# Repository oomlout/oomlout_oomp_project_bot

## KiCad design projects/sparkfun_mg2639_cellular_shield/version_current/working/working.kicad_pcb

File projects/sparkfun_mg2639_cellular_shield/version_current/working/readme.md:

# OOMP Project  
## MG2639_Cellular_Shield  by sparkfun  
  
oomp key: oomp_projects_flat_sparkfun_mg2639_cellular_shield  
(snippet of original readme)  
  
**Note:Retired Product**  
This product has been retired from our catalog and is no longer for sale. This page is made available for those looking for datasheets and the simply curious.  
  
SparkFun MG2639 Cellular Shield  
=========================  

[*SparkFun MG2639 Cellular Shield (CEL-13120)*](https://www.sparkfun.com/products/13120)  
  
The SparkFun MG2639 Cellular shield is an Arduino compatible shield that gives the user access to the MG2639_V3 GSM+GPS module. The module is capable of accquiring a GPS location as well as communication with GSM networks all over the world. Phonecalls can be made, texts sent, and data pushed to and read from web pages. All the supporting circuitry is provided including translation from 2.8V of the module to a user selectable 3.3V or 5V.  
  
The main interface is two software serial ports.  
  
Power can be provided either from the Arduino board's VIN or from an external battery such as a lithium polymer.  
  
Repository Contents  
-------------------  
  
* **/Firmware** - Example sketches that work without the Arduino library.  
* **/Hardware** - Schematic and PCB layout for the shield. Also includes an eagle library containing the various custom footprints for this shield. Specifically the MG2639 footprint.  
* **/Documentation** - The AT command set, hardware guide, and various other datasheets.  
* **/Libr  
  full source readme at [readme_src.md](readme_src.md)  
  
source repo at: [https://github.com/sparkfun/MG2639_Cellular_Shield](https://github.com/sparkfun/MG2639_Cellular_Shield)  
## Board  

## Schematic  

[schematic pdf](working_schematic.pdf)  
## Images

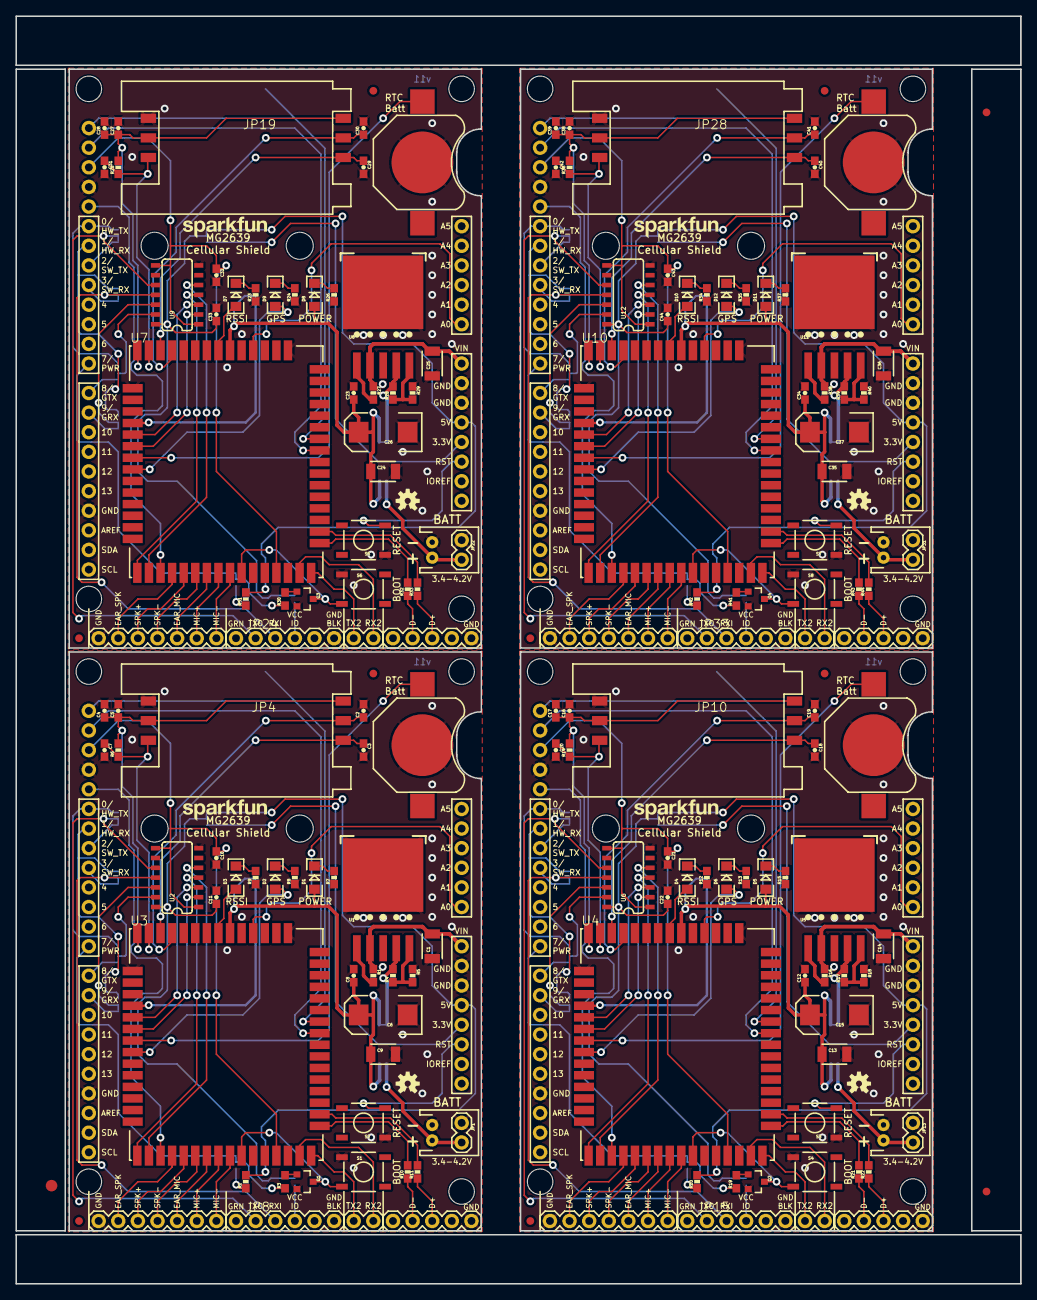
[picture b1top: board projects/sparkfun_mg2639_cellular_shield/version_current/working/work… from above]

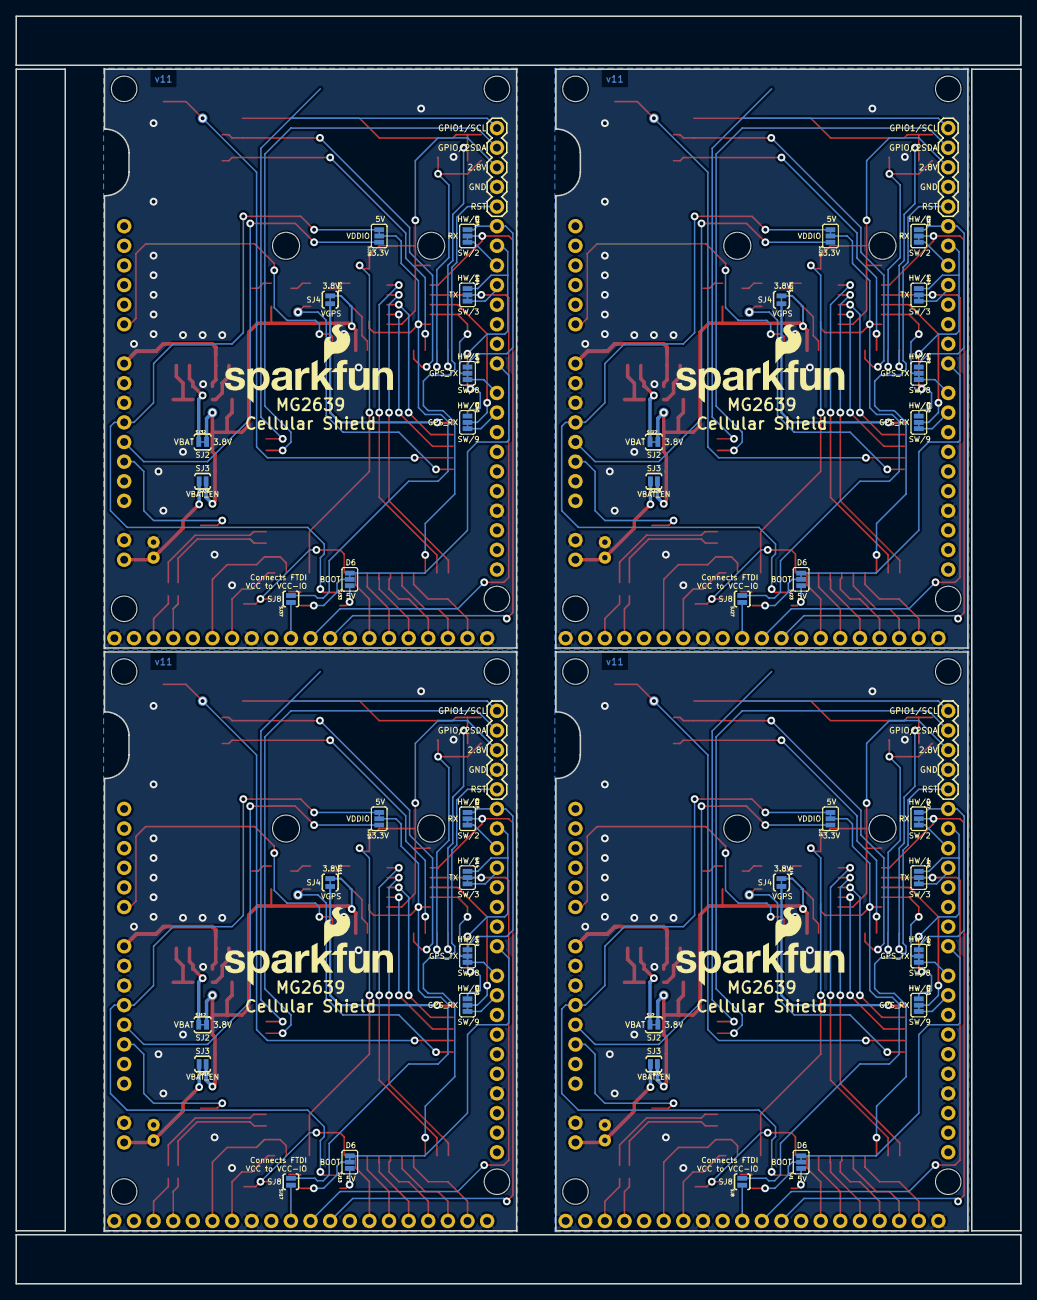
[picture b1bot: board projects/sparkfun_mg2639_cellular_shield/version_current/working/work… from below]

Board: 2 copper layers, 130.0 x 164.1 mm, 263 parts (60 on the bottom side), 236 nets.

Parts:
@HOLE0, @HOLE1, @HOLE2, @HOLE3, @HOLE4, @HOLE5, @HOLE6, @HOLE7: (no value)
BAT1, BAT2, BAT3, BAT4: 12mm coincell; BATTCON_12MM
C1, C9, C13, C14, C24, C25, C35, C36: 10uF; 1210
C2, C3, C7, C18, C19, C20, C29, C30, C31, C40, C41, C42: 33pF; 0603-CAP
C4, C17, C28, C39: 1.0uF; 0603-CAP
C5, C8, C10, C11, C12, C16, C21, C22, C23, C27, C32, C33, C34, C38, C43, C44: 0.1uF; 0603-CAP
C6, C15, C26, C37: 100uF; EIA7343
D1, D5, D8, D11: RED; LED-1206
D2, D6, D9, D12: YELLOW; LED-1206
D3, D4, D7, D10: GREEN; LED-1206
E$1: FIDUCIAL-1.5X3
E$4, E$5: FIDUCIAL-1X2
FID1, FID2, FID3, FID4, FID5, FID6, FID7, FID8: FIDUCIAL1X2; FIDUCIAL-1X2
JP1, JP13, JP22, JP31: LiPo; JST-2-PTH
JP2, JP16, JP25, JP34: M02PTH; 1X02
JP3, JP11, JP20, JP29: ARDUINO_R3_SHIELD; UNO_R3_SHIELD_NOLABELS
JP4, JP10, JP19, JP28: SIMHOLDER
JP5, JP12, JP21, JP30: AUDIO; 1X07
JP6, JP18, JP27, JP36: MISC; 1X05
JP7, JP17, JP26, JP35: UART2; 1X02
JP8, JP15, JP24, JP33: FTDI_BASICPTH; FTDI_BASIC
JP9, JP14, JP23, JP32: USB; 1X05
LOGO1, LOGO6, LOGO9, LOGO12: SFE_LOGO_NAME.1_INCH; SFE_LOGO_NAME_.1
LOGO2, LOGO5, LOGO8, LOGO11: SFE_LOGO_NAME_FLAME.2_INCH; SFE_LOGO_NAME_FLAME_.2
LOGO3, LOGO4, LOGO7, LOGO10: OSHW-LOGOS; OSHW-LOGO-S
Q1, Q2, Q3, Q4: MMBT2222A; SOT23-3
R1, R6, R14, R16, R25, R27, R36, R38: 10K; 0603-RES
R2, R5, R7, R8, R9, R12, R13, R15, R18, R20, R23, R24, R26, R29, R31, R34, R35, R37, R40, R42: 1K; 0603-RES
R3, R19, R30, R41: 4.7K; 0603
R4, R17, R28, R39: 2.2k; 0603-RES
R10, R11, R21, R22, R32, R33, R43, R44: 22; 0603-RES
S1, S4, S6, S8: BOOT; TACTILE-SWITCH-SMD
S2, S3, S5, S7: RESET; TACTILE-SWITCH-SMD
SJ1, SJ13, SJ23, SJ33: BOOT; PAD-JUMPER-3-2OF3_NC_BY_TRACE_YES_SILK_FULL_BOX
SJ2, SJ12, SJ22, SJ32: VBAT1; PAD-JUMPER-2-NC_BY_TRACE_YES_SILK
SJ3, SJ18, SJ28, SJ38: VBAT_EN; PAD-JUMPER-2-NO_YES_SILK
SJ4, SJ11, SJ21, SJ31: PAD-JUMPER-2-NC_BY_TRACE_YES_SILK
SJ5, SJ6, SJ7, SJ9, SJ10, SJ14, SJ15, SJ16, SJ19, SJ20, SJ24, SJ25, SJ26, SJ29, SJ30, SJ34, SJ35, SJ36, SJ39, SJ40: PAD-JUMPER-3-2OF3_NC_BY_TRACE_YES_SILK_FULL_BOX
SJ8, SJ17, SJ27, SJ37: FTDI_VCCIO; PAD-JUMPER-2-NO_YES_SILK
STANDOFF1, STANDOFF2, STANDOFF3, STANDOFF4, STANDOFF5, STANDOFF6, STANDOFF7, STANDOFF8, STANDOFF9, STANDOFF10, STANDOFF11, STANDOFF12, STANDOFF13, STANDOFF14, STANDOFF15, STANDOFF16: STAND-OFF
TP1, TP2, TP3, TP4, TP5, TP6, TP7, TP8, TP9, TP10, TP11, TP12: PAD.03X.05
U1, U5, U8, U11: SPX29302; Q5-DD_SPX29300
U2, U6, U9, U12: TXB0104; SO14
U3, U4, U7, U10: MG2639V3; MG2639

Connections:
3.3V: JP3.3.3V, SJ5.1
3.3V1: JP11.3.3V, SJ16.1
3.3V2: JP20.3.3V, SJ26.1
3.3V3: JP29.3.3V, SJ36.1
3.8V: C6.A, C8.1, C9.1, D1.A, SJ2.2, SJ3.1, SJ4.1, TP3.P$1, U3.6
3.8V1: C12.1, C13.1, C15.A, D5.A, SJ11.1, SJ12.2, SJ18.1, TP6.P$1, U4.6
3.8V2: C23.1, C24.1, C26.A, D8.A, SJ21.1, SJ22.2, SJ28.1, TP9.P$1, U7.6
3.8V3: C34.1, C35.1, C37.A, D11.A, SJ31.1, SJ32.2, SJ38.1, TP12.P$1, U10.6
5V: JP3.5V, R2.2, SJ5.3
5V1: JP11.5V, R20.2, SJ16.3
5V2: JP20.5V, R31.2, SJ26.3
5V3: JP29.5V, R42.2, SJ36.3
ADJUST: R4.1, R5.2, U1.5
ADJUST1: R17.1, R18.2, U5.5
ADJUST2: R28.1, R29.2, U8.5
ADJUST3: R39.1, R40.2, U11.5
EAR_L: JP5.6, U3.32
EAR_L1: JP12.6, U4.32
EAR_L2: JP21.6, U7.32
EAR_L3: JP30.6, U10.32
GND: BAT1.GND, C1.1, C2.2, C3.2, C4.2, C5.2, C6.C, C7.2, C8.2, C9.2, C10.2, C11.2, JP1.1, JP2.1, JP3.GND@0, JP3.GND@1, JP3.GND@2, JP4.C5, JP5.7, JP6.4, JP8.GND, JP9.1, Q1.2, R5.1, R7.1, R8.1, R9.1, S1.1, S2.1, U1.3, U1.6, U2.7, U3.1, U3.3, U3.5, U3.15, U3.17, U3.42
GND1: BAT2.GND, C12.2, C13.2, C14.1, C15.C, C16.2, C17.2, C18.2, C19.2, C20.2, C21.2, C22.2, JP10.C5, JP11.GND@0, JP11.GND@1, JP11.GND@2, JP12.7, JP13.1, JP14.1, JP15.GND, JP16.1, JP18.4, Q2.2, R12.1, R13.1, R15.1, R18.1, S3.1, S4.1, U4.1, U4.3, U4.5, U4.15, U4.17, U4.42, U5.3, U5.6, U6.7
GND2: BAT3.GND, C23.2, C24.2, C25.1, C26.C, C27.2, C28.2, C29.2, C30.2, C31.2, C32.2, C33.2, JP19.C5, JP20.GND@0, JP20.GND@1, JP20.GND@2, JP21.7, JP22.1, JP23.1, JP24.GND, JP25.1, JP27.4, Q3.2, R23.1, R24.1, R26.1, R29.1, S5.1, S6.1, U7.1, U7.3, U7.5, U7.15, U7.17, U7.42, U8.3, U8.6, U9.7
GND3: BAT4.GND, C34.2, C35.2, C36.1, C37.C, C38.2, C39.2, C40.2, C41.2, C42.2, C43.2, C44.2, JP28.C5, JP29.GND@0, JP29.GND@1, JP29.GND@2, JP30.7, JP31.1, JP32.1, JP33.GND, JP34.1, JP36.4, Q4.2, R34.1, R35.1, R37.1, R40.1, S7.1, S8.1, U10.1, U10.3, U10.5, U10.15, U10.17, U10.42, U11.3, U11.6, U12.7
GPIO1/SCL: JP6.1, U3.54
GPIO1/SCL1: JP18.1, U4.54
GPIO1/SCL2: JP27.1, U7.54
GPIO1/SCL3: JP36.1, U10.54
GPIO2/SDA: JP6.2, U3.53
GPIO2/SDA1: JP18.2, U4.53
GPIO2/SDA2: JP27.2, U7.53
GPIO2/SDA3: JP36.2, U10.53
GPS_FIX: D2.A, TP1.P$1, U3.22
GPS_FIX1: D6.A, TP4.P$1, U4.22
GPS_FIX2: D9.A, TP7.P$1, U7.22
GPS_FIX3: D12.A, TP10.P$1, U10.22
GPS_RTC: BAT1.PWR@1, TP2.P$1, U3.21
GPS_RTC1: BAT2.PWR@1, TP5.P$1, U4.21
GPS_RTC2: BAT3.PWR@1, TP8.P$1, U7.21
GPS_RTC3: BAT4.PWR@1, TP11.P$1, U10.21
GRX-2.8V: U2.3, U3.19
GRX-2.8V1: U4.19, U6.3
GRX-2.8V2: U7.19, U9.3
GRX-2.8V3: U10.19, U12.3
GRX-HV: SJ10.2, U2.12
GRX-HV1: SJ20.2, U6.12
GRX-HV2: SJ30.2, U9.12
GRX-HV3: SJ40.2, U12.12
GRX-SOFT: JP3.D9, SJ10.3
GRX-SOFT1: JP11.D9, SJ20.3
GRX-SOFT2: JP20.D9, SJ30.3
GRX-SOFT3: JP29.D9, SJ40.3
GTX-2.8V: U2.2, U3.20
GTX-2.8V1: U4.20, U6.2
GTX-2.8V2: U7.20, U9.2
GTX-2.8V3: U10.20, U12.2
GTX-HV: SJ9.2, U2.13
GTX-HV1: SJ19.2, U6.13
GTX-HV2: SJ29.2, U9.13
GTX-HV3: SJ39.2, U12.13
GTX-SOFT: JP3.D8, SJ9.3
GTX-SOFT1: JP11.D8, SJ19.3
GTX-SOFT2: JP20.D8, SJ29.3
GTX-SOFT3: JP29.D8, SJ39.3
MIC_N0: JP5.1, U3.37
MIC_N1: JP12.1, U4.37
MIC_N2: JP21.1, U7.37
MIC_N3: JP30.1, U10.37
MIC_P0: JP5.2, U3.36
MIC_P1: JP5.3, U3.35
MIC_P2: JP12.3, U4.35
MIC_P3: JP12.2, U4.36
MIC_P4: JP21.3, U7.35
MIC_P5: JP21.2, U7.36
MIC_P6: JP30.3, U10.35
MIC_P7: JP30.2, U10.36
unnamed: R1.2, U1.1
unnamed: JP9.4, R10.1
unnamed: Q1.1, R3.2
unnamed: R4.2, SJ2.1, U1.4
unnamed: R3.1, SJ1.2
unnamed: R2.1, SJ1.1
unnamed: D3.A, U3.7
unnamed: D3.C, R9.2
unnamed: D2.C, R8.2
unnamed: JP9.3, R11.1
unnamed: JP8.VCC, SJ8.1
unnamed: JP1.2, JP2.2, SJ3.2
unnamed: D5.C, R15.2
unnamed: R16.2, U5.1
unnamed: Q2.1, R19.2
unnamed: R19.1, SJ13.2
unnamed: D1.C, R7.2
unnamed: D4.A, U4.7
unnamed: D4.C, R12.2
unnamed: D6.C, R13.2
unnamed: R17.2, SJ12.1, U5.4
unnamed: R20.1, SJ13.1
unnamed: JP14.4, R21.1
unnamed: JP14.3, R22.1
unnamed: JP15.VCC, SJ17.1
unnamed: JP13.2, JP16.2, SJ18.2
unnamed: D8.C, R26.2
unnamed: R27.2, U8.1
unnamed: Q3.1, R30.2
unnamed: R30.1, SJ23.2
unnamed: D7.A, U7.7
unnamed: D7.C, R23.2
unnamed: D9.C, R24.2
unnamed: R28.2, SJ22.1, U8.4
unnamed: R31.1, SJ23.1
unnamed: JP23.4, R32.1
unnamed: JP23.3, R33.1
unnamed: JP24.VCC, SJ27.1
unnamed: JP22.2, JP25.2, SJ28.2
unnamed: D11.C, R37.2
unnamed: R38.2, U11.1
unnamed: Q4.1, R41.2
unnamed: R41.1, SJ33.2
unnamed: D10.A, U10.7
unnamed: D10.C, R34.2
unnamed: D12.C, R35.2
unnamed: R39.2, SJ32.1, U11.4
unnamed: R42.1, SJ33.1
unnamed: JP32.4, R43.1
unnamed: JP32.3, R44.1
unnamed: JP33.VCC, SJ37.1
unnamed: JP31.2, JP34.2, SJ38.2
ON/OFF: JP3.D7, SJ1.3
ON/OFF1: JP11.D7, SJ13.3
ON/OFF2: JP20.D7, SJ23.3
ON/OFF3: JP29.D7, SJ33.3
RECN: JP5.4, U3.34
RECN1: JP12.4, U4.34
RECN2: JP21.4, U7.34
RECN3: JP30.4, U10.34
RECP: JP5.5, U3.33
RECP1: JP12.5, U4.33
RECP2: JP21.5, U7.33
RECP3: JP30.5, U10.33
RESET: JP3.RES, S2.3
RESET1: JP11.RES, S3.3
RESET2: JP20.RES, S5.3
RESET3: JP29.RES, S7.3
RING: JP3.A0, U3.4
RING1: JP11.A0, U4.4
RING2: JP20.A0, U7.4
RING3: JP29.A0, U10.4
RX2-2.8V: JP7.1, U3.43
RX2-2.8V1: JP17.1, U4.43
RX2-2.8V2: JP26.1, U7.43
RX2-2.8V3: JP35.1, U10.43
RX-2.8V: U2.4, U3.29
RX-2.8V1: U4.29, U6.4
RX-2.8V2: U7.29, U9.4
RX-2.8V3: U10.29, U12.4
RX-HV: JP8.TXO, SJ6.2, U2.11
RX-HV1: JP15.TXO, SJ14.2, U6.11
RX-HV2: JP24.TXO, SJ24.2, U9.11
RX-HV3: JP33.TXO, SJ34.2, U12.11
RX-SOFT: JP3.D3, SJ6.3
RX-SOFT1: JP11.D3, SJ14.3
RX-SOFT2: JP20.D3, SJ24.3
RX-SOFT3: JP29.D3, SJ34.3
RXI: JP3.RX, SJ7.1, SJ9.1
RXI1: JP11.RX, SJ15.1, SJ19.1
RXI2: JP20.RX, SJ25.1, SJ29.1
RXI3: JP29.RX, SJ35.1, SJ39.1
SIM_CLK: C3.1, JP4.C3, U3.12
SIM_CLK1: C18.1, JP10.C3, U4.12
SIM_CLK2: C29.1, JP19.C3, U7.12
SIM_CLK3: C40.1, JP28.C3, U10.12
SIM_DATA: C7.1, JP4.C7, R6.1, U3.13
SIM_DATA1: C20.1, JP10.C7, R14.1, U4.13
SIM_DATA2: C31.1, JP19.C7, R25.1, U7.13
SIM_DATA3: C42.1, JP28.C7, R36.1, U10.13
SIM_RST: C2.1, JP4.C2, U3.11
SIM_RST1: C19.1, JP10.C2, U4.11
SIM_RST2: C30.1, JP19.C2, U7.11
SIM_RST3: C41.1, JP28.C2, U10.11
TX2-2.8V: JP7.2, U3.44
TX2-2.8V1: JP17.2, U4.44
TX2-2.8V2: JP26.2, U7.44
TX2-2.8V3: JP35.2, U10.44
TX-2.8V: U2.5, U3.30
TX-2.8V1: U4.30, U6.5
TX-2.8V2: U7.30, U9.5
TX-2.8V3: U10.30, U12.5
TX-HV: JP8.RXI, SJ7.2, U2.10
TX-HV1: JP15.RXI, SJ15.2, U6.10
TX-HV2: JP24.RXI, SJ25.2, U9.10
TX-HV3: JP33.RXI, SJ35.2, U12.10
TX-SOFT: JP3.D2, SJ7.3
TX-SOFT1: JP11.D2, SJ15.3
TX-SOFT2: JP20.D2, SJ25.3
TX-SOFT3: JP29.D2, SJ35.3
TXO: JP3.TX, SJ6.1, SJ10.1
TXO1: JP11.TX, SJ14.1, SJ20.1
TXO2: JP20.TX, SJ24.1, SJ30.1
TXO3: JP29.TX, SJ34.1, SJ40.1
USB+: R11.2, U3.46
USB+1: R22.2, U4.46
USB+2: R33.2, U7.46
USB+3: R44.2, U10.46
USB-: R10.2, U3.45
USB-1: R21.2, U4.45
USB-2: R32.2, U7.45
USB-3: R43.2, U10.45
VCCB: C11.1, SJ5.2, SJ8.2, U2.14
VCCB1: C22.1, SJ16.2, SJ17.2, U6.14
VCCB2: C33.1, SJ26.2, SJ27.2, U9.14
VCCB3: C44.1, SJ36.2, SJ37.2, U12.14
VDDIO: C10.1, JP6.3, U2.1, U2.8, U3.41
VDDIO1: C21.1, JP18.3, U4.41, U6.1, U6.8
VDDIO2: C32.1, JP27.3, U7.41, U9.1, U9.8
VDDIO3: C43.1, JP36.3, U10.41, U12.1, U12.8
VRAW: C1.2, JP3.VIN, R1.1, U1.2
VRAW1: C14.2, JP11.VIN, R16.1, U5.2
VRAW2: C25.2, JP20.VIN, R27.1, U8.2
VRAW3: C36.2, JP29.VIN, R38.1, U11.2
VSIM: C4.1, C5.1, JP4.C1, JP4.C6, R6.2, U3.14
VSIM1: C16.1, C17.1, JP10.C1, JP10.C6, R14.2, U4.14
VSIM2: C27.1, C28.1, JP19.C1, JP19.C6, R25.2, U7.14
VSIM3: C38.1, C39.1, JP28.C1, JP28.C6, R36.2, U10.14
V_GPS: SJ4.2, U3.18
V_GPS1: SJ11.2, U4.18
V_GPS2: SJ21.2, U7.18
V_GPS3: SJ31.2, U10.18
~PWRKEY1: Q2.3, S4.3, U4.38
~PWRKEY2: Q3.3, S6.3, U7.38
~PWRKEY3: Q4.3, S8.3, U10.38
~PWRKEY: Q1.3, S1.3, U3.38
~SYSRST1: JP18.5, U4.31
~SYSRST2: JP27.5, U7.31
~SYSRST3: JP36.5, U10.31
~SYSRST: JP6.5, U3.31

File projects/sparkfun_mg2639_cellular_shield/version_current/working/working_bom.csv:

Row,Description,Part,References,Value,Footprint,Quantity Per PCB,Status,Datasheet
1,,BATTERY12MM,BAT1,12mm coincell,BATTCON_12MM,1, ,
2,,33PF-50V-5%-(0603),C2 C3 C7,33pF,0603-CAP,3, ,
3,,0.1UF-25V(+80/-20%)(0603),C5 C8 C10 C11,0.1uF,0603-CAP,4, ,
4,,1.0UF-16V-10%(0603),C4,1.0uF,0603-CAP,1, ,
5,,10UF50V20%(1210),C1 C9,10uF,1210,2, ,
6,,100UF-10V-10%(TANT),C6,100uF,EIA7343,1, ,
7,,LED-GREENLARGE,D3,GREEN,LED-1206,1, ,
8,,LED-RED1206,D1,RED,LED-1206,1, ,
9,,LED-YELLOWLARGE,D2,YELLOW,LED-1206,1, ,
10,,FRAME-LEDGER,FRAME1,FRAME-LEDGER,CREATIVE_COMMONS,1, ,
11,,ARDUINO_R3_SHIELDNOLABELS,JP3,ARDUINO_R3_SHIELDNOLABELS,UNO_R3_SHIELD_NOLABELS,1, ,
12,,M07,JP5,AUDIO,1X07,1, ,
13,,FTDI_BASICPTH,JP8,FTDI_BASICPTH,FTDI_BASIC,1, ,
14,,M02JST-PTH-2,JP1,M02JST-PTH-2,JST-2-PTH,1, ,
15,,M02PTH,JP2 JP7,M02PTH,1X02,2, ,
16,,M05PTH,JP6,MISC,1X05,1, ,
17,,SIMHOLDERSIM,JP4,SIMHOLDER,SIMHOLDER,1, ,
18,,M05PTH,JP9,USB,1X05,1, ,
19,,OSHW-LOGOS,LOGO3,OSHW-LOGOS,OSHW-LOGO-S,1, ,
20,,SFE_LOGO_NAME.1_INCH,LOGO1,SFE_LOGO_NAME.1_INCH,SFE_LOGO_NAME_.1,1, ,
21,,SFE_LOGO_NAME_FLAME.2_INCH,LOGO2,SFE_LOGO_NAME_FLAME.2_INCH,SFE_LOGO_NAME_FLAME_.2,1, ,
22,,TRANSISTOR_NPNMMBT2222A,Q1,MMBT2222A,SOT23-3,1, ,
23,,22OHM1/10W1%(0603),R10 R11,22,0603-RES,2, ,
24,,1KOHM1/10W1%(0603),R2 R5 R7 R8 R9,1K,0603-RES,5, ,
25,,2.2KOHM1/10W1%(0603),R4,2.2k,0603-RES,1, ,
26,,4.7KOHM1/10W1%(0603),R3,4.7K,0603,1, ,
27,,10KOHM1/10W1%(0603)0603,R1 R6,10K,0603-RES,2, ,
28,,SWITCH-MOMENTARY-2SMD,S1 S2,SWITCH-MOMENTARY-2SMD,TACTILE-SWITCH-SMD,2, ,
29,,JUMPER-PAD-2-NC_BY_TRACE,SJ2 SJ4,JUMPER-PAD-2-NC_BY_TRACE,PAD-JUMPER-2-NC_BY_TRACE_YES_SILK,2, ,
30,,JUMPER-PAD-2-NOYES_SILK,SJ3 SJ8,JUMPER-PAD-2-NOYES_SILK,PAD-JUMPER-2-NO_YES_SILK,2, ,
31,,JUMPER-PAD-3-2OF3_NC_BY_TRACE,SJ1 SJ5 SJ6 SJ7 SJ9 SJ10,JUMPER-PAD-3-2OF3_NC_BY_TRACE,PAD-JUMPER-3-2OF3_NC_BY_TRACE_YES_SILK_FULL_BOX,6, ,
32,,STAND-OFF,STANDOFF1 STANDOFF2 STANDOFF3 STANDOFF4,STAND-OFF,STAND-OFF,4, ,
33,,MG2639V3,U3,MG2639V3,MG2639,1, ,
34,,SPX29302,U1,SPX29302,Q5-DD_SPX29300,1, ,
35,,TXB0104PWRSOIC14,U2,TXB0104,SO14,1, ,





Project info:
Schematic:,working
Variant:,default
Revision:,
Date:,2023-08-06_12-56-06
KiCad Version:,7.0.6-7.0.6~ubuntu22.04.1
Statistics:
Component Groups:,35
Component Count:,59 (0 SMD/ 0 THT)
Fitted Components:,59 (0 SMD/ 0 THT)
Number of PCBs:,1
Total Components:,59

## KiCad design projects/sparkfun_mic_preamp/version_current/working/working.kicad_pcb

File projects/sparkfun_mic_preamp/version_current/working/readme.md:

# OOMP Project  
## Mic_Preamp  by sparkfun  
  
oomp key: oomp_projects_flat_sparkfun_mic_preamp  
(snippet of original readme)  
  
Mic_Preamp  
==========  
[  
*SparkFun Mic Preamp (PRT-08872)*](https://www.sparkfun.com/products/8872)  
  
This breakout is a simple microphone preamp circuit for a wide range of microphone types.   
It enables you to attach mics to your larger stereo amplifier.  
  
Repository Contents  
-------------------  
* **/Hardware** - All Eagle design files (.brd, .sch)  

License Information  
-------------------  
The hardware is released under [Creative Commons ShareAlike 4.0 International](https://creativecommons.org/licenses/by-sa/4.0/).  
  
Distributed as-is; no warranty is given.  
  full source readme at [readme_src.md](readme_src.md)  
  
source repo at: [https://github.com/sparkfun/Mic_Preamp](https://github.com/sparkfun/Mic_Preamp)  
## Board  

## Schematic  

[schematic pdf](working_schematic.pdf)  
## Images

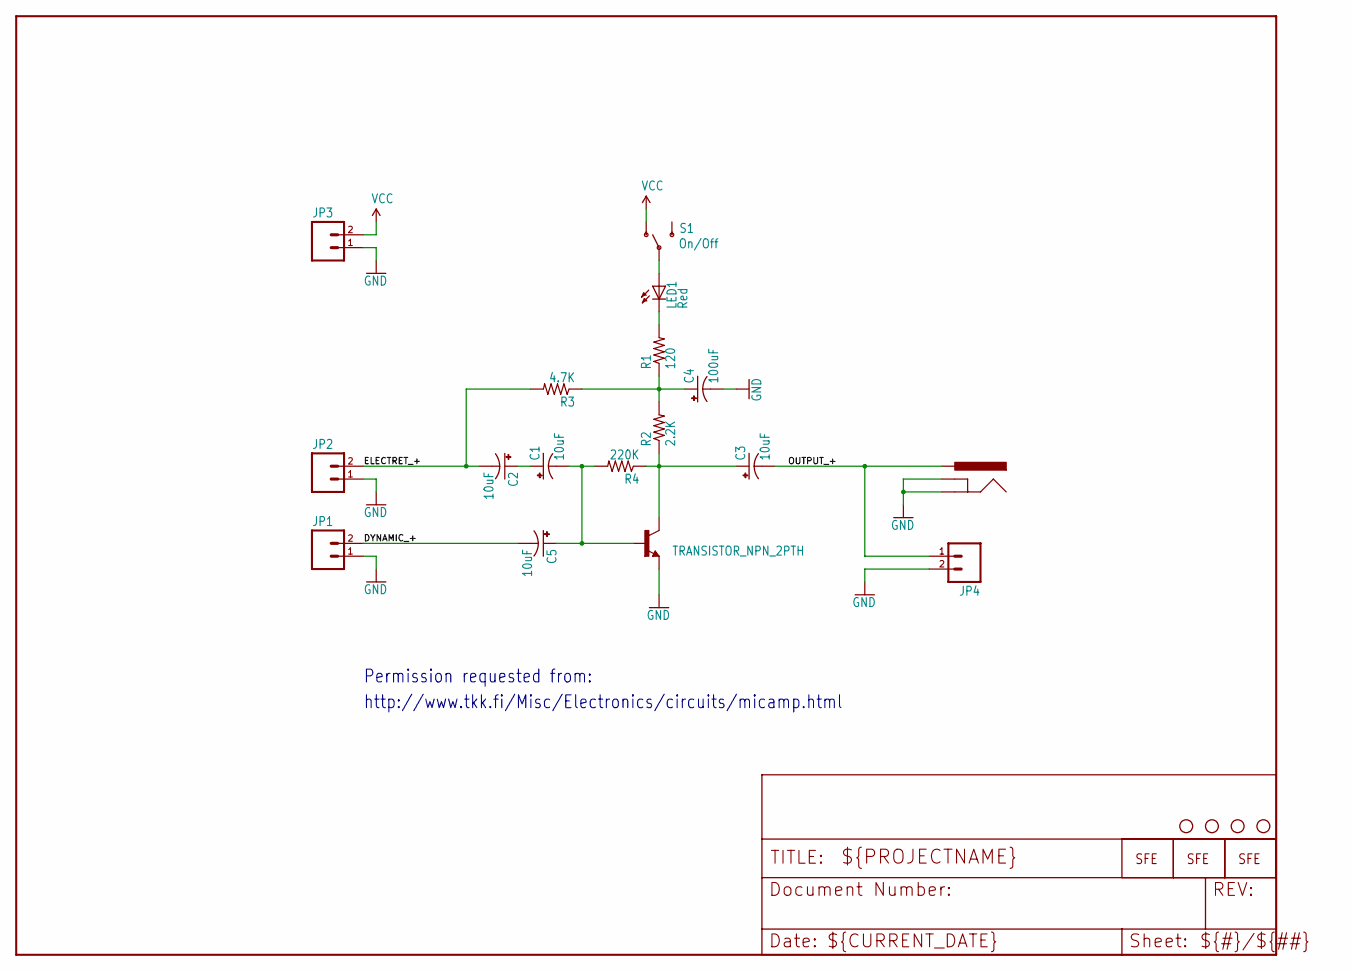
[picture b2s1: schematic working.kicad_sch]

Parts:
C1, C2, C3, C5: 10uF; CPOL-RADIAL-10UF-25V
C4: 100uF; CPOL-RADIAL-100UF-25V
J1: POWER_JACKRCA_LOCK; RCA_LOCK
JP1, JP2, JP3, JP4: M02PTH; 1X02
JP6: LOGO-SFENW2; SFE-NEW-WEB
LED1: Red; LED5MM
Q1: TRANSISTOR_NPN_2PTH; TO-92
R1: 120; AXIAL-0.3
R2: 2.2K; AXIAL-0.3
R3: 4.7K; AXIAL-0.3
R4: 220K; AXIAL-0.3
S1: On/Off; SWITCH-SPDT_LOCK.007S
U$1, U$6: LOGO-SFESK; SFE-LOGO-FLAME
U$2, U$3, U$4, U$5: STAND-OFF

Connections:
DYNAMIC_+: C5.2 (-), JP1.2
ELECTRET_+: C2.2 (-), JP2.2, R3.P$2 (2)
GND: C4.2 (-), J1.BARREL (GND), J1.SPRING (GNDBREAK), JP1.1, JP2.1, JP3.1, JP4.2, Q1.3 (E)
unnamed: LED1.K (C), R1.P$2 (2)
unnamed: C3.1 (+), Q1.1 (C), R2.P$1 (1), R4.P$1 (1)
unnamed: C4.1 (+), R1.P$1 (1), R2.P$2 (2), R3.P$1 (1)
unnamed: C1.2 (-), C5.1 (+), Q1.2 (B), R4.P$2 (2)
unnamed: C1.1 (+), C2.1 (+)
unnamed: LED1.A, S1.2
OUTPUT_+: C3.2 (-), J1.BREAK (PWR), JP4.1
VCC: JP3.2, S1.1 (O)

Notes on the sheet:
Permission requested from:
http://www.tkk.fi/Misc/Electronics/circuits/micamp.html

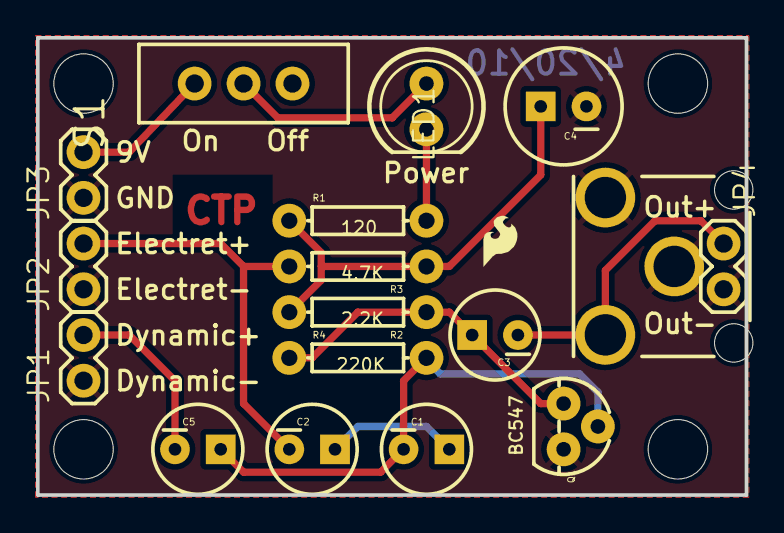
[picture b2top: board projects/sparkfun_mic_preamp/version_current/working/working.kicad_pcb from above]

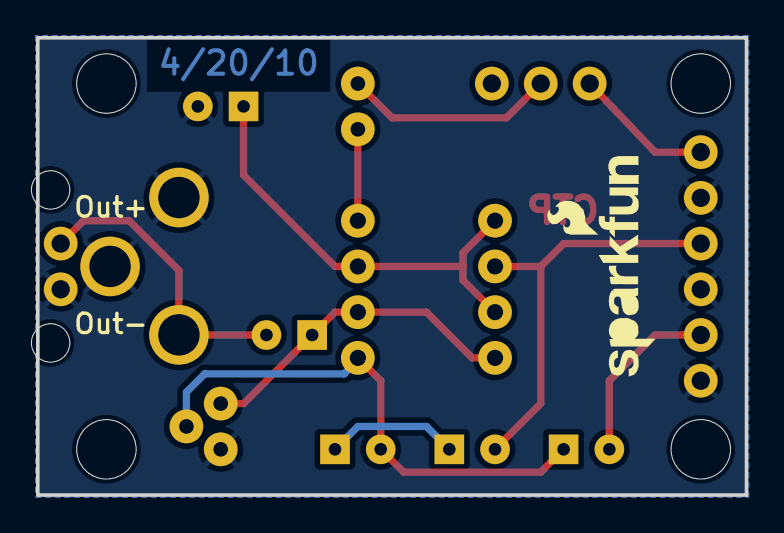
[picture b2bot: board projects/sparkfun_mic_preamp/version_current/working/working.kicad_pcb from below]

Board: 2 copper layers, 39.4 x 25.4 mm, 24 parts (2 on the bottom side), 11 nets.

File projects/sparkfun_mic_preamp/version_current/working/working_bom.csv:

"Id";"Designator";"Footprint";"Quantity";"Designation";"Supplier and ref";
1;"U$3,U$5,U$4,U$2";"STAND-OFF";4;"STAND-OFF";;;
2;"C2,C3,C1,C5";"CPOL-RADIAL-10UF-25V";4;"10uF";;;
3;"R3";"AXIAL-0.3";1;"4.7K";;;
4;"S1";"SWITCH-SPDT_LOCK.007S";1;"On/Off";;;
5;"LED1";"LED5MM";1;"Red";;;
6;"JP4,JP2,JP3,JP1";"1X02";4;"";;;
7;"C4";"CPOL-RADIAL-100UF-25V";1;"100uF";;;
8;"J1";"RCA_LOCK";1;"POWER_JACKRCA_LOCK";;;
9;"R1";"AXIAL-0.3";1;"120";;;
10;"R2";"AXIAL-0.3";1;"2.2K";;;
11;"Q1";"TO-92";1;"TRANSISTOR_NPN_2PTH";;;
12;"R4";"AXIAL-0.3";1;"220K";;;
13;"U$1,U$6";"SFE-LOGO-FLAME";2;"LOGO-SFESK";;;
14;"JP6";"SFE-NEW-WEB";1;"LOGO-SFENW2";;;

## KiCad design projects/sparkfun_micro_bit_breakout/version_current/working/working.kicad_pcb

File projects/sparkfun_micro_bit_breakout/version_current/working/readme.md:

# Micro_Bit_Breakout by sparkfun  
This is a harvested standardized copy of a project from github.  
The original project can be found at:  
https://github.com/sparkfun/Micro_Bit_Breakout  
Please consult that link for additional, details, files, and license information.  
Note: It was auto harvested and if the original repo had more than one board file or anything out of the ordinary the files here are likely not representative.

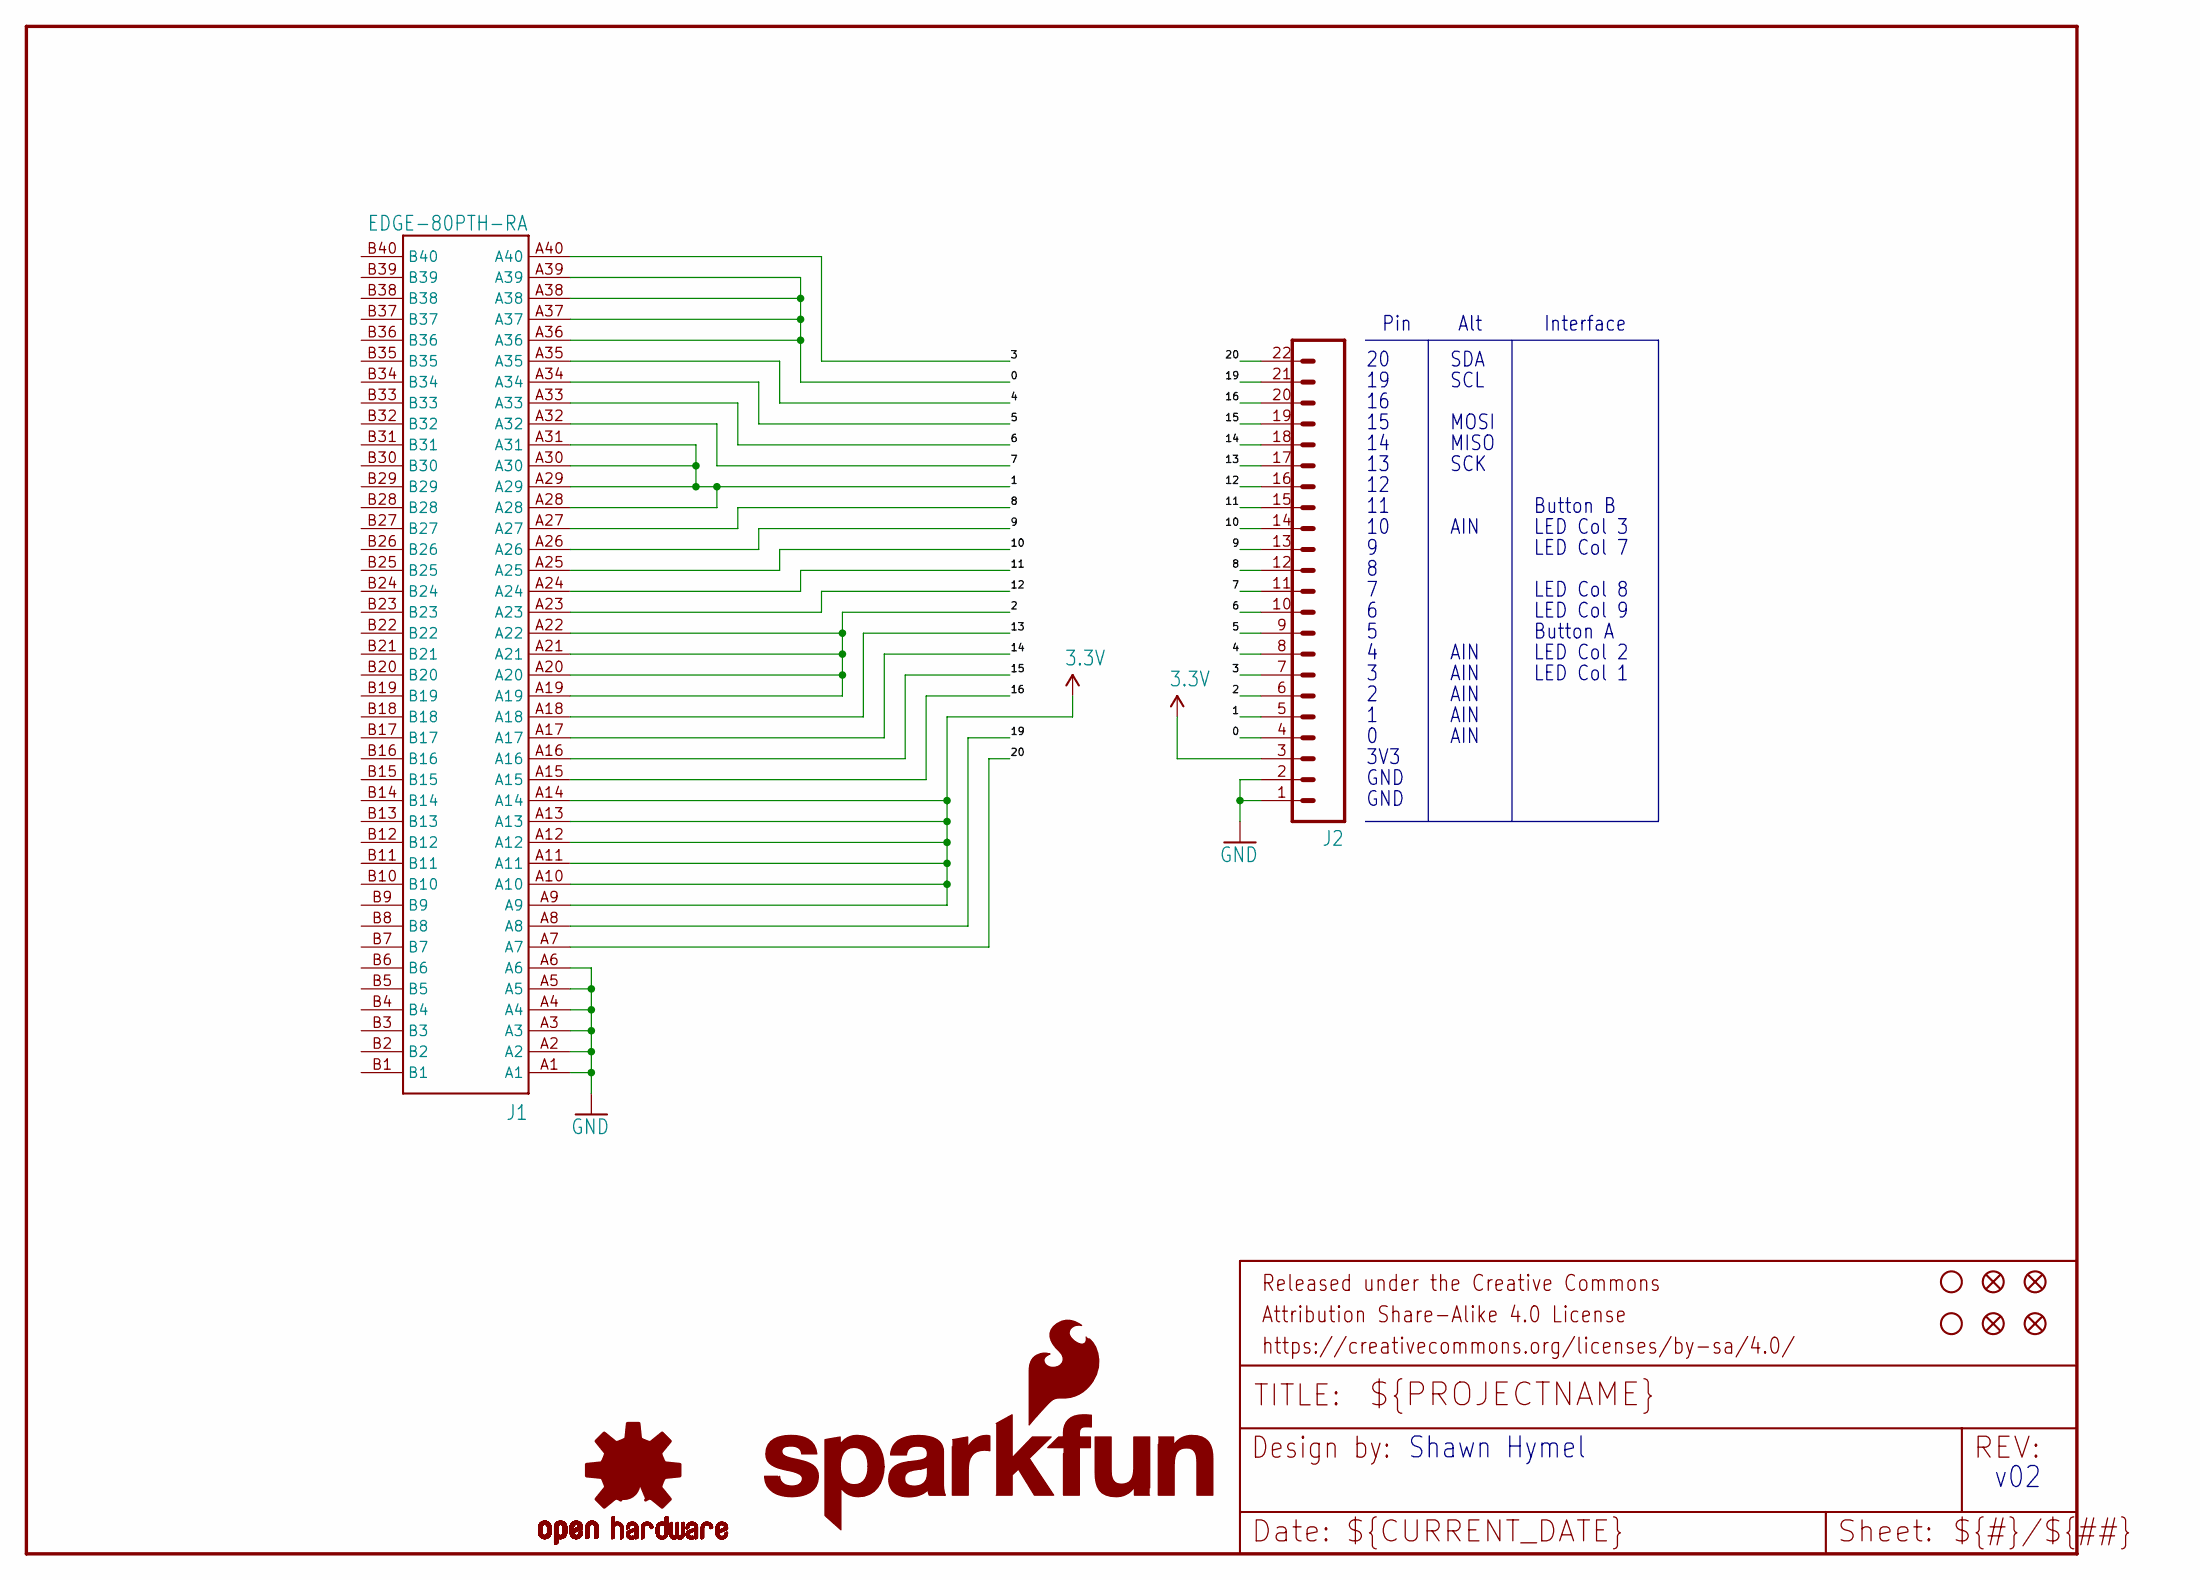
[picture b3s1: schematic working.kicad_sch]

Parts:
FD1, FD2, FD3, FD4: FIDUCIAL1X2; FIDUCIAL-1X2
FRAME1: FRAME-LETTER; CREATIVE_COMMONS
H1, H2: STAND-OFF
J1: EDGE-80PTH-RA; VEC-127-080-R
J2: M22PTH; 1X22
LOGO2: SFE_LOGO_NAME_FLAME.1_INCH; SFE_LOGO_NAME_FLAME_.1
LOGO3: OSHW-LOGOS; OSHW-LOGO-S

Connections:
0: J1.A36, J1.A37, J1.A38, J1.A39, J2.4
1: J1.A28, J1.A29, J1.A30, J1.A31, J2.5
2: J1.A19, J1.A20, J1.A21, J1.A22, J2.6
3: J1.A40, J2.7
3.3V: J1.A9, J1.A10, J1.A11, J1.A12, J1.A13, J1.A14, J2.3
4: J1.A35, J2.8
5: J1.A34, J2.9
6: J1.A33, J2.10
7: J1.A32, J2.11
8: J1.A27, J2.12
9: J1.A26, J2.13
10: J1.A25, J2.14
11: J1.A24, J2.15
12: J1.A23, J2.16
13: J1.A18, J2.17
14: J1.A17, J2.18
15: J1.A16, J2.19
16: J1.A15, J2.20
19: J1.A8, J2.21
20: J1.A7, J2.22
GND: J1.A1, J1.A2, J1.A3, J1.A4, J1.A5, J1.A6, J2.1, J2.2

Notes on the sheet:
LED Col 1
GND
LED Col 3
Pin
LED Col 2
3V3
AIN
SCL
MISO
Shawn Hymel
Button B
MOSI
LED Col 7
Alt
SDA
Button A
LED Col 9
LED Col 8
SCK
Interface
v02

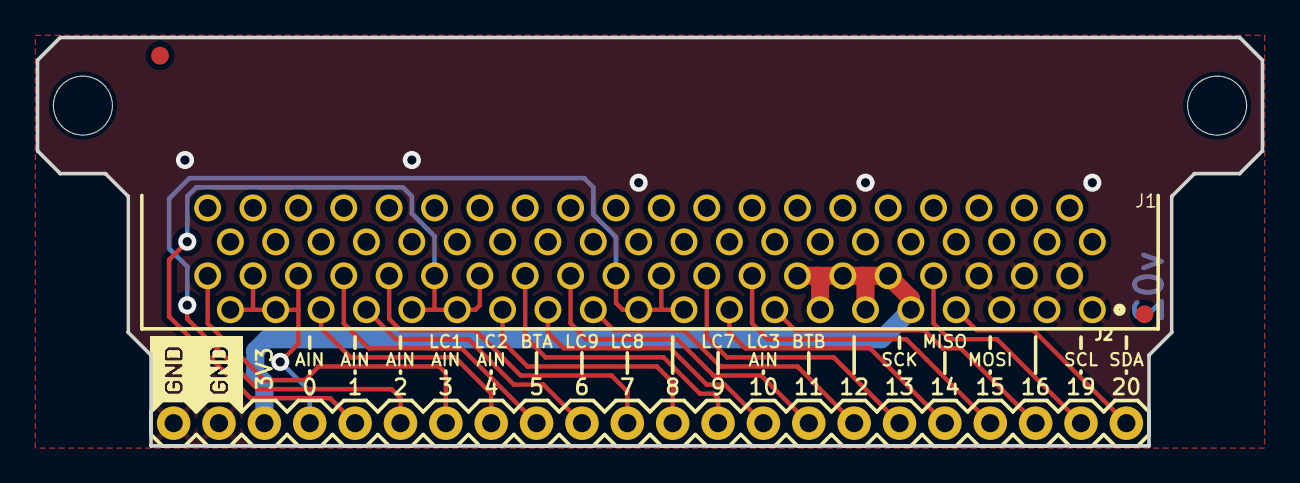
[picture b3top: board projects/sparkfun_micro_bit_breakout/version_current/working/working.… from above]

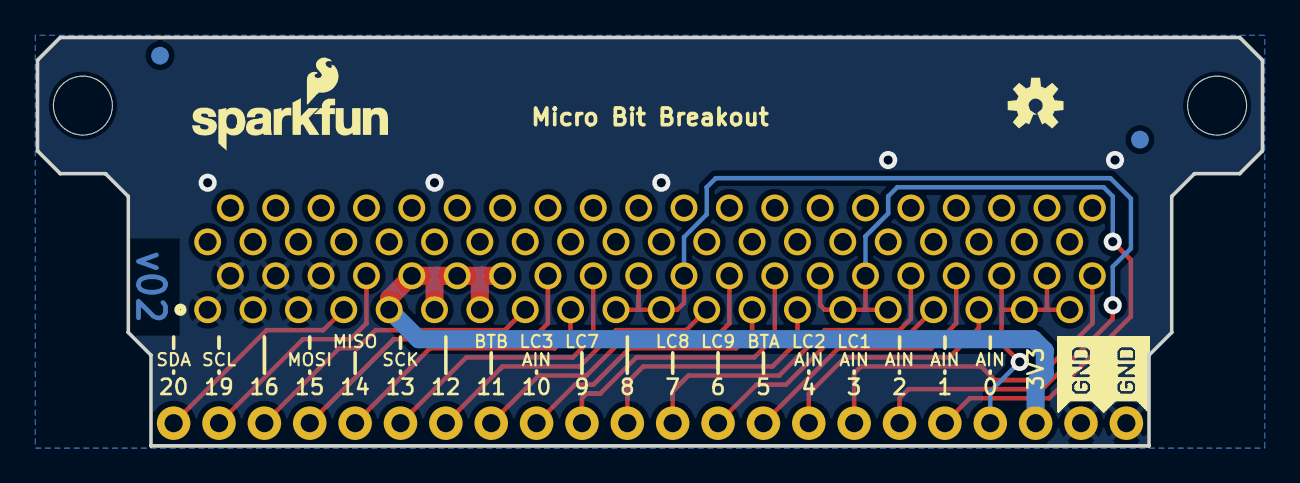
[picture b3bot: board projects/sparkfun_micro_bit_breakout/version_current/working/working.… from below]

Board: 4 copper layers, 68.6 x 22.9 mm, 13 parts (5 on the bottom side), 21 nets.

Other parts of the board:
U$1, U$2: NEGASILK_MICRO_BIT_BREAKOUT

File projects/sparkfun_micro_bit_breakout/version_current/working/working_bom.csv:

"Id";"Designator";"Footprint";"Quantity";"Designation";"Supplier and ref";
1;"FD2,FD1,FD3,FD4";"FIDUCIAL-1X2";4;"FIDUCIAL1X2";;;
2;"H1,H2";"STAND-OFF";2;"STAND-OFF";;;
3;"FRAME1";"CREATIVE_COMMONS";1;"FRAME-LETTER";;;
4;"J1";"VEC-127-080-R";1;"EDGE-80PTH-RA";;;
5;"U$1,U$2";"NEGASILK_MICRO_BIT_BREAKOUT";2;"";;;
6;"J2";"1X22";1;"M22PTH";;;
7;"LOGO2";"SFE_LOGO_NAME_FLAME_.1";1;"SFE_LOGO_NAME_FLAME.1_INCH";;;
8;"LOGO3";"OSHW-LOGO-S";1;"OSHW-LOGOS";;;

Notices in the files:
projects/sparkfun_mg2639_cellular_shield/version_current/working/working.kicad_sch:
Released under the Creative Commons
parts and their libraries:
Released under the Creative Commons Attribution Share-Alike 4.0 License
